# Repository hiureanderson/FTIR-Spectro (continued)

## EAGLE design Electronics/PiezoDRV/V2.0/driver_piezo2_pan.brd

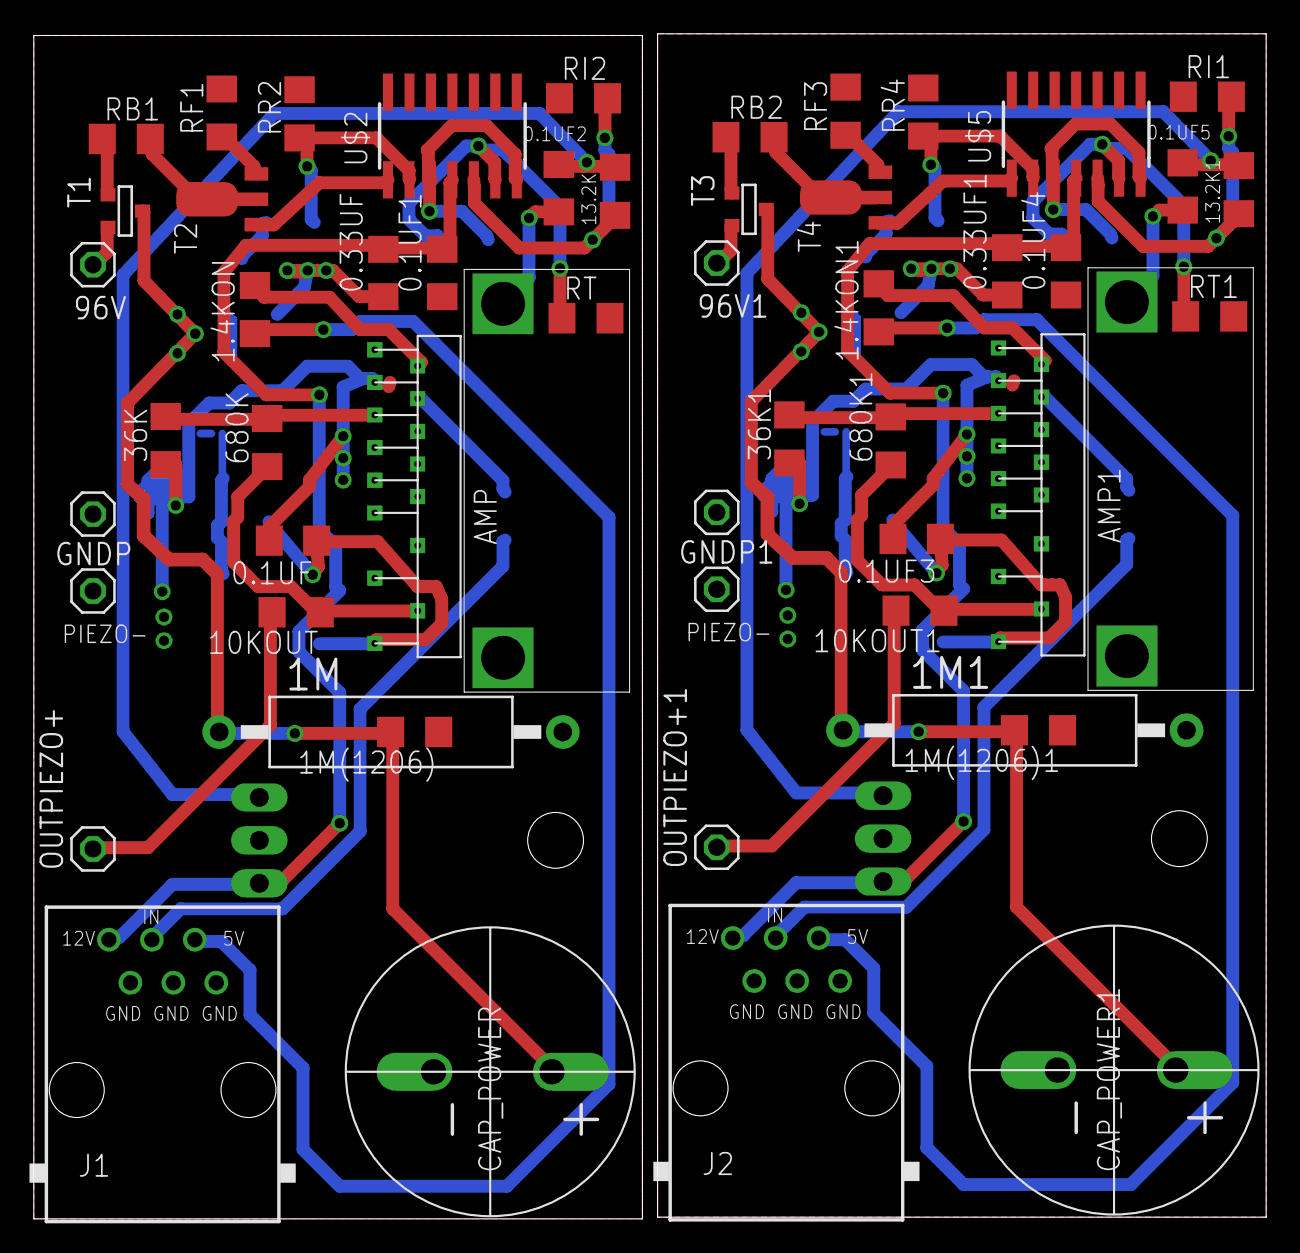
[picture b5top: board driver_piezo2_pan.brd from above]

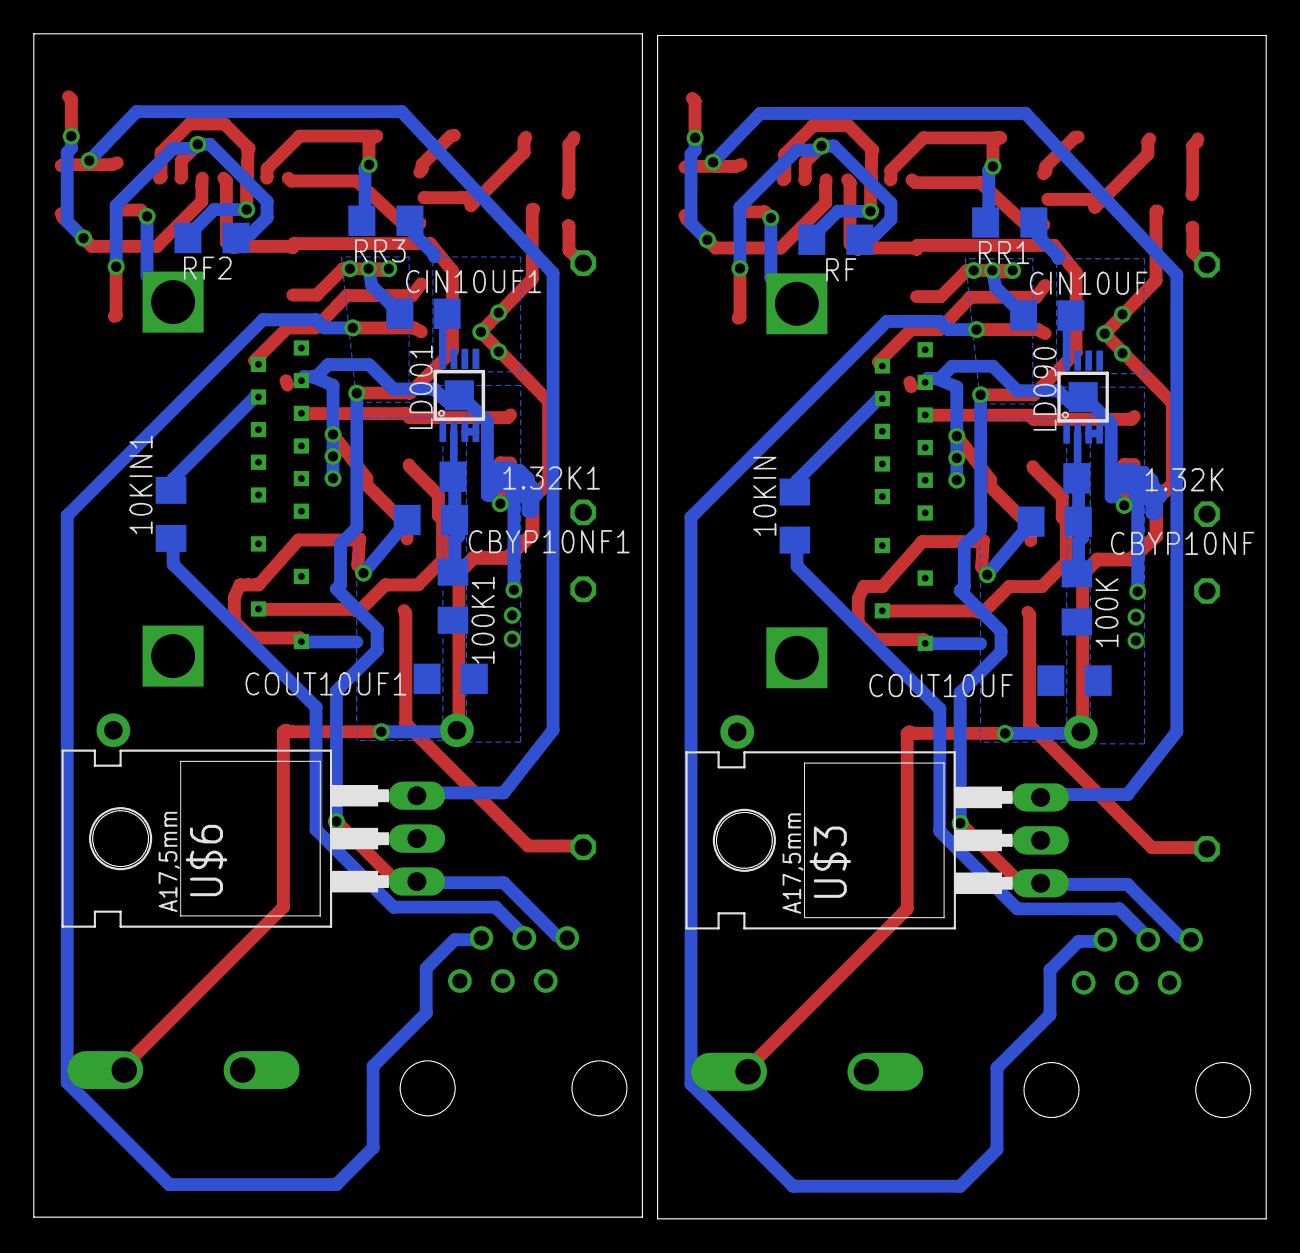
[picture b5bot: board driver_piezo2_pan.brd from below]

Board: 2 copper layers, 72.9 x 70.1 mm, 74 parts (20 on the bottom side), 44 nets.

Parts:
0.1UF, 0.1UF1, 0.1UF2, 0.1UF3, 0.1UF4, 0.1UF5, 0.33UF, 0.33UF1: C1206
1.4KON, 1.4KON1, 1.32K, 1.32K1, 1M(1206), 1M(1206)1, 10KIN, 10KIN1, 10KOUT, 10KOUT1, 36K, 36K1, 100K, 100K1, 680K, 680K1: R1206
1M, 1M1: CA0002
13.2K, 13.2K1: 13.2K; R1206
96V, 96V1: 1X01
AMP, AMP1: POWER_AMP_LME49811TB
CAP_POWER, CAP_POWER1: CAP200VCAP200V; CAP200V
CBYP10NF, CBYP10NF1: C1206
CIN10UF, CIN10UF1: C1206
COUT10UF, COUT10UF1: C1206
GND1, GND2: 1X01
GNDP, GNDP1: 1X01
J1, J2: RJ12STRAIGHT-ANALOG; RJ12-STRAIGHT-ANALOG
LD001, LD090: TPS7A4001; S-PDSO-G08
OUTPIEZO+, OUTPIEZO+1: 1X01
RB1, RB2: 100k; R1206
RF, RF1, RF2, RF3: 10k; R1206
RI1, RI2: 280k; R1206
RR1, RR3: 810k-806k; R1206
RR2, RR4: 90k; R1206
RT, RT1: 10k; R1206
T1, T3: FMMT718; SOT-23
T2, T4: SOT89
U$1, U$4: DISIPADOR
U$2, U$5: LM324; SO14
U$3, U$6: 7805; TO220

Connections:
1OUT: T2.1, U$2.1
1OUT1: T4.1, U$5.1
2IN+: 13.2K.1, RI2.2, U$2.5
2IN+1: 13.2K1.1, RI1.2, U$5.5
2IN-: RF.1, RT.1, U$2.6
2IN-1: RF2.1, RT1.1, U$5.6
2OUT: RF.2, U$2.3, U$2.7
2OUT1: RF2.2, U$5.3, U$5.7
5V: 1.4KON.1, J1.+5V
5V1: 1.4KON1.1, J2.+5V
5VOP: 0.1UF2.2, 13.2K.2, U$3.3
5VOP1: 0.1UF5.2, 13.2K1.2, U$6.3
12V: 0.1UF1.2, 0.33UF.2, J1.+12V, U$2.4, U$3.1
12V1: 0.1UF4.2, 0.33UF1.2, J2.+12V, U$5.4, U$6.1
B: 36K.2, 680K.2, AMP.IN-
B1: 36K1.2, 680K1.2, AMP1.IN-
FB: 1.32K.2, 100K.1, CBYP10NF.2, LD090.2
FB1: 1.32K1.2, 100K1.1, CBYP10NF1.2, LD001.2
GND: 0.1UF.2, 0.1UF1.1, 0.1UF2.1, 0.33UF.1, 1.32K.1, 1M.2, 1M(1206).1, 36K.1, AMP.-VEE, AMP.GND, CAP_POWER.-, CIN10UF.1, COUT10UF.2, GND2.1, GNDP.1, J1.GND1, J1.GND2, J1.GND3, LD090.3, LD090.4, LD090.TH, RF1.2, RI2.1, RR2.2, RT.2, U$1.P$1, U$1.P$2, U$2.11, U$3.2
GND1: 0.1UF3.2, 0.1UF4.1, 0.1UF5.1, 0.33UF1.1, 1.32K1.1, 1M1.2, 1M(1206)1.1, 36K1.1, AMP1.-VEE, AMP1.GND, CAP_POWER1.-, CIN10UF1.1, COUT10UF1.2, GND1.1, GNDP1.1, J2.GND1, J2.GND2, J2.GND3, LD001.3, LD001.4, LD001.TH, RF3.2, RI1.1, RR4.2, RT1.2, U$4.P$1, U$4.P$2, U$5.11, U$6.2
IN_AMP: 10KIN.2, AMP.IN+
IN_AMP1: 10KIN1.2, AMP1.IN+
IN_VOLTAGE: 10KIN.1, J1.IN
IN_VOLTAGE1: 10KIN1.1, J2.IN
unnamed: RB2.2, T4.2, T4.2@1
unnamed: RB2.1, T3.3
unnamed: RB1.2, T2.2, T2.2@1
unnamed: RB1.1, T1.3
unnamed: RF1.1, T2.3
unnamed: RF3.1, T4.3
ON: 1.4KON.2, AMP.SD
ON1: 1.4KON1.2, AMP1.SD
OUT_PIEZO: 10KOUT.2, OUTPIEZO+.1
OUT_PIEZO1: 10KOUT1.2, OUTPIEZO+1.1
SOURCE: 10KOUT.1, 680K.1, AMP.SOURCE
SOURCE1: 10KOUT1.1, 680K1.1, AMP1.SOURCE
V1: 0.1UF3.1, 100K1.2, AMP1.VCC, CBYP10NF1.1, COUT10UF1.1, LD001.1
V90: 0.1UF.1, 100K.2, AMP.VCC, CBYP10NF.1, COUT10UF.1, LD090.1
VF: RR1.2, RR2.1, U$2.2
VF1: RR3.2, RR4.1, U$5.2
VIN: 1M.1, 1M(1206).2, CAP_POWER.+, CIN10UF.2, LD090.5, LD090.8, RR1.1, T1.1
VIN1: 1M1.1, 1M(1206)1.2, CAP_POWER1.+, CIN10UF1.2, LD001.5, LD001.8, RR3.1, T3.1
VINS: 96V.1, T1.2
VINS1: 96V1.1, T3.2

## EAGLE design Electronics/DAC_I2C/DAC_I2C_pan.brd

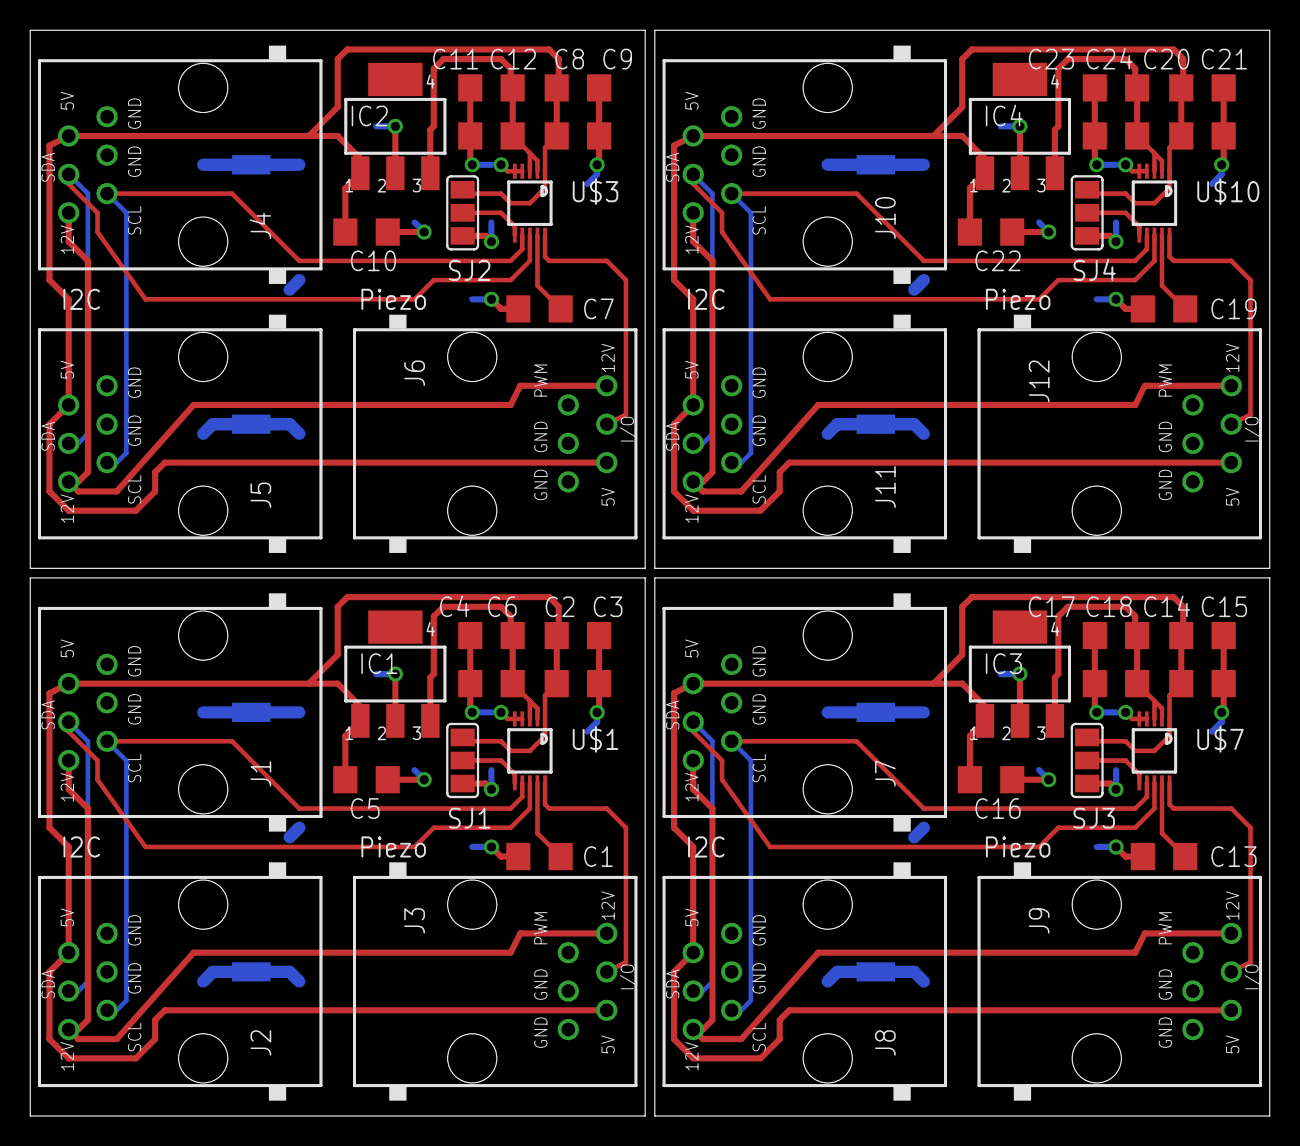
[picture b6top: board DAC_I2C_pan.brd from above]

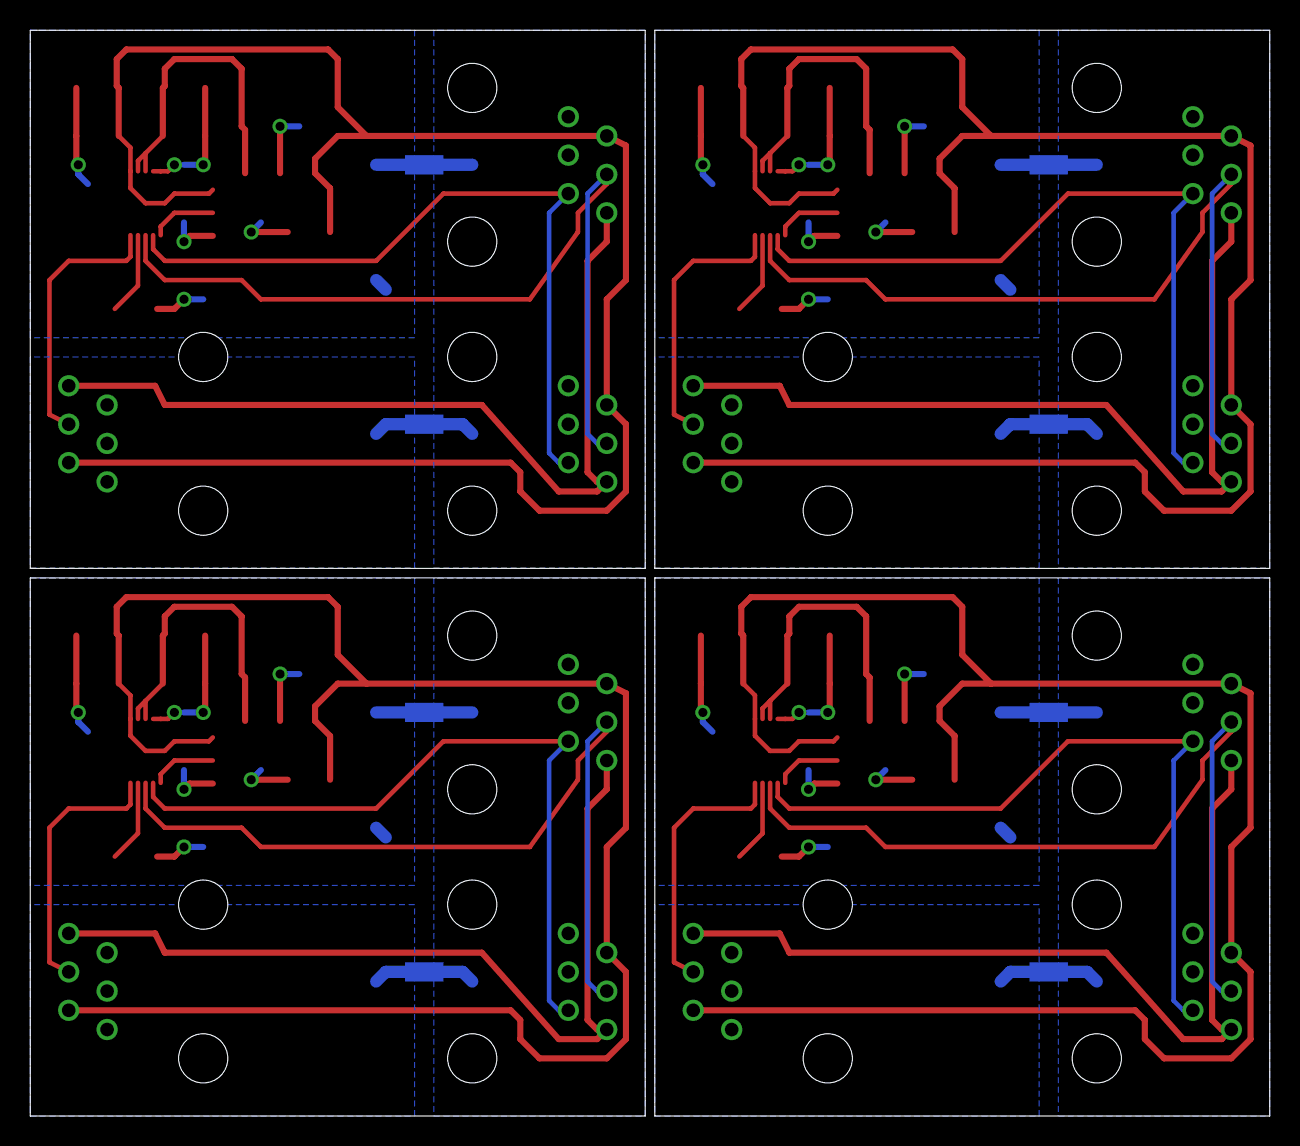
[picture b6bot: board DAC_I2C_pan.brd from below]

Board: 2 copper layers, 81.9 x 71.8 mm, 56 parts (8 on the bottom side), 44 nets.

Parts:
C1, C7, C13, C19: 10n; C1206
C2, C6, C8, C12, C14, C18, C20, C24: 100n; C1206
C3, C9, C15, C21: 10u; C1206
C4, C5, C10, C11, C16, C17, C22, C23: 10uF; C1206
IC1, IC2, IC3, IC4: MCP1703DB; SOT223
J1, J2, J4, J5, J7, J8, J10, J11: RJ12STRAIGHT-I2C; RJ12-STRAIGHT-I2C
J3, J6, J9, J12: RJ12STRAIGHT; RJ12-STRAIGHT
SJ1, SJ2, SJ3, SJ4: SJ_2
U$1, U$3, U$7, U$10: AD5693R; MSOP10
U$2, U$4, U$5, U$6, U$8, U$9, U$11, U$12: STARGND; STAR

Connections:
3.3V: C4.1, C6.1, IC1.3, U$1.2, U$1.3
3.3V1: C11.1, C12.1, IC2.3, U$3.2, U$3.3
3.3V2: C17.1, C18.1, IC3.3, U$7.2, U$7.3
3.3V3: C23.1, C24.1, IC4.3, U$10.2, U$10.3
AGND: C1.2, C2.2, C3.2, C4.2, C5.2, C6.2, IC1.2, SJ1.3, U$1.4, U$1.5, U$5.AGND
AGND1: C7.2, C8.2, C9.2, C10.2, C11.2, C12.2, IC2.2, SJ2.3, U$3.4, U$3.5, U$4.AGND
AGND2: C13.2, C14.2, C15.2, C16.2, C17.2, C18.2, IC3.2, SJ3.3, U$7.4, U$7.5, U$8.AGND
AGND3: C19.2, C20.2, C21.2, C22.2, C23.2, C24.2, IC4.2, SJ4.3, U$10.4, U$10.5, U$11.AGND
DGND: J1.GND1, J1.GND2, J2.GND1, J2.GND2, U$2.DGND, U$2.GND, U$5.DGND, U$5.GND
DGND1: J4.GND1, J4.GND2, J5.GND1, J5.GND2, U$4.DGND, U$4.GND, U$6.DGND, U$6.GND
DGND2: J7.GND1, J7.GND2, J8.GND1, J8.GND2, U$8.DGND, U$8.GND, U$9.DGND, U$9.GND
DGND3: J10.GND1, J10.GND2, J11.GND1, J11.GND2, U$11.DGND, U$11.GND, U$12.DGND, U$12.GND
GND: J3.GND1, J3.GND2, U$2.AGND
GND1: J6.GND1, J6.GND2, U$6.AGND
GND2: J9.GND1, J9.GND2, U$9.AGND
GND3: J12.GND1, J12.GND2, U$12.AGND
unnamed: SJ1.2, U$1.6
unnamed: SJ2.2, U$3.6
unnamed: SJ3.2, U$7.6
unnamed: SJ4.2, U$10.6
SCL: J1.SCL, J2.SCL, U$1.7
SCL1: J4.SCL, J5.SCL, U$3.7
SCL2: J7.SCL, J8.SCL, U$7.7
SCL3: J10.SCL, J11.SCL, U$10.7
SDA: J1.SDA, J2.SDA, U$1.8
SDA1: J4.SDA, J5.SDA, U$3.8
SDA2: J7.SDA, J8.SDA, U$7.8
SDA3: J10.SDA, J11.SDA, U$10.8
VCC: C2.1, C3.1, C5.1, IC1.1, J1.+5V, J2.+5V, J3.+5V, SJ1.1, U$1.1
VCC1: C8.1, C9.1, C10.1, IC2.1, J4.+5V, J5.+5V, J6.+5V, SJ2.1, U$3.1
VCC2: C14.1, C15.1, C16.1, IC3.1, J7.+5V, J8.+5V, J9.+5V, SJ3.1, U$7.1
VCC3: C20.1, C21.1, C22.1, IC4.1, J10.+5V, J11.+5V, J12.+5V, SJ4.1, U$10.1
VDD: J1.+12V, J2.+12V, J3.+12V
VDD1: J4.+12V, J5.+12V, J6.+12V
VDD2: J7.+12V, J8.+12V, J9.+12V
VDD3: J10.+12V, J11.+12V, J12.+12V
VOUT: J3.I/O, U$1.10
VOUT1: J6.I/O, U$3.10
VOUT2: J9.I/O, U$7.10
VOUT3: J12.I/O, U$10.10
VREF: C1.1, U$1.9
VREF1: C7.1, U$3.9
VREF2: C13.1, U$7.9
VREF3: C19.1, U$10.9

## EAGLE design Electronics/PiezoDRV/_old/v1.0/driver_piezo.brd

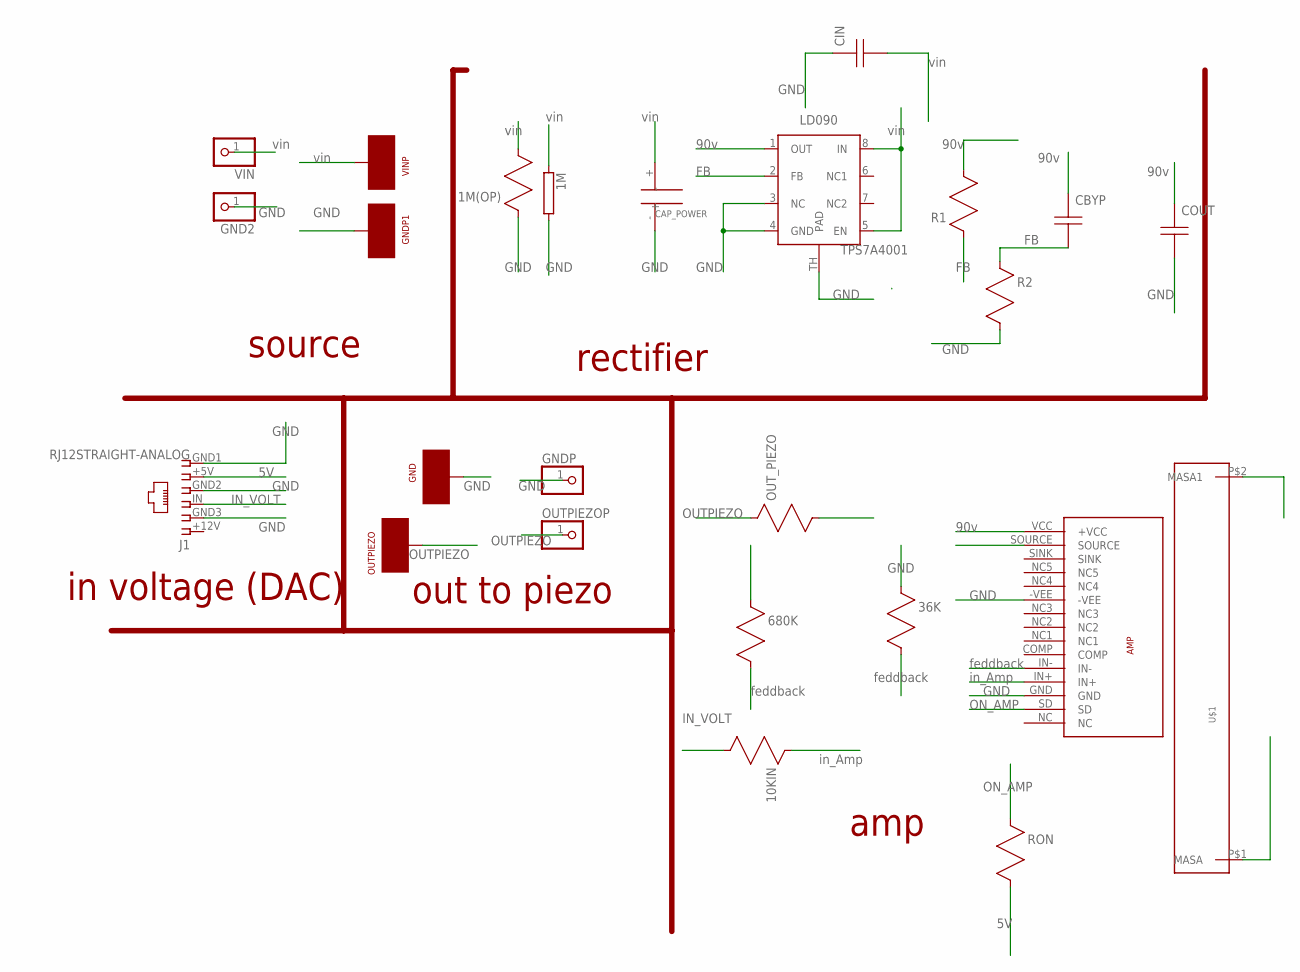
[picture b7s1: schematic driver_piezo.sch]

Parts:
1M: RCA0002; CA0002
1M(OP), 10KIN, 36K, 680K: RES; R0805
AMP: POWER_AMP_LME49811TB
CAP_POWER: CAP200VCAP200V; CAP200V
CBYP: CAP; C0805
CIN: CAP; C0805
COUT: CAP; C0805
GND: PAD
GND2: PINHD-1X1; 1X01
GNDP: PINHD-1X1; 1X01
GNDP1: PAD
J1: RJ12STRAIGHT-ANALOG; RJ12-STRAIGHT-ANALOG
LD090: TPS7A4001; S-PDSO-G08
OUTPIEZO: PAD
OUTPIEZOP: PINHD-1X1; 1X01
OUT_PIEZO: RES; R0805
R1, R2: RES; R0805
RON: RES; R0805
U$1: DISIPADOR
VIN: PINHD-1X1; 1X01
VINP: PAD

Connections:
5V: J1.+5V (5), RON.2 (B)
B: 36K.2 (B), 680K.2 (B), AMP.IN-
FB: CBYP.2 (B), LD090.2 (FB), R1.1 (A), R2.1 (A)
GND: 1M.2, 1M(OP).1 (A), 36K.1 (A), AMP.-VEE, AMP.GND, CAP_POWER.-, CIN.1 (A), COUT.2 (B), GND.P$1, GND2.1, GNDP.1, GNDP1.P$1, J1.GND1 (6), J1.GND2 (4), J1.GND3 (2), LD090.3 (NC), LD090.4 (GND), LD090.TH (PAD), R2.2 (B), U$1.P$1 (MASA), U$1.P$2 (MASA1)
IN_AMP: 10KIN.1 (A), AMP.IN+
IN_VOLTAGE: 10KIN.2 (B), J1.IN (3)
ON: AMP.SD, RON.1 (A)
OUT_PIEZO: OUTPIEZO.P$1, OUTPIEZOP.1, OUT_PIEZO.1 (A)
SOURCE: 680K.1 (A), AMP.SOURCE, OUT_PIEZO.2 (B)
V90: AMP.VCC (+VCC), CBYP.1 (A), COUT.1 (A), LD090.1 (OUT), R1.2 (B)
VIN: 1M.1, 1M(OP).2 (B), CAP_POWER.+, CIN.2 (B), LD090.5 (EN), LD090.8 (IN), VIN.1, VINP.P$1

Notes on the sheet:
source
rectifier
out to piezo
amp
vin
90v
GND
OUTPIEZO
IN_VOLT
ON_AMP
feddback
in voltage (DAC)
in_Amp

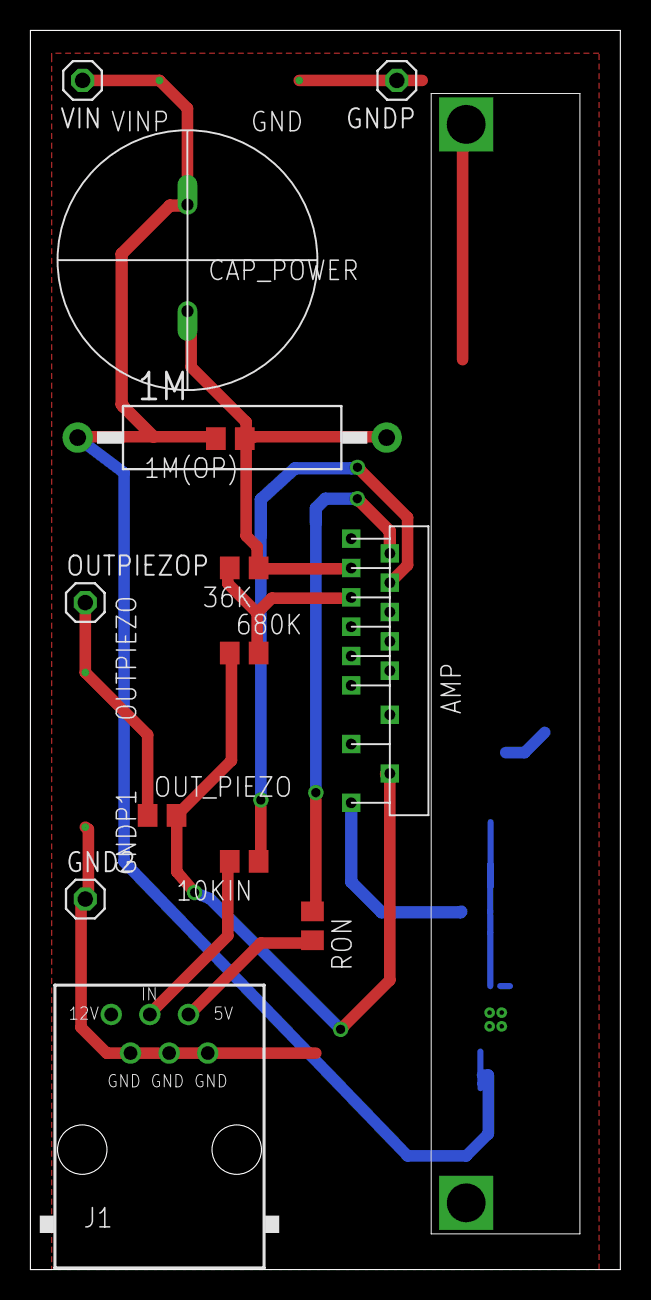
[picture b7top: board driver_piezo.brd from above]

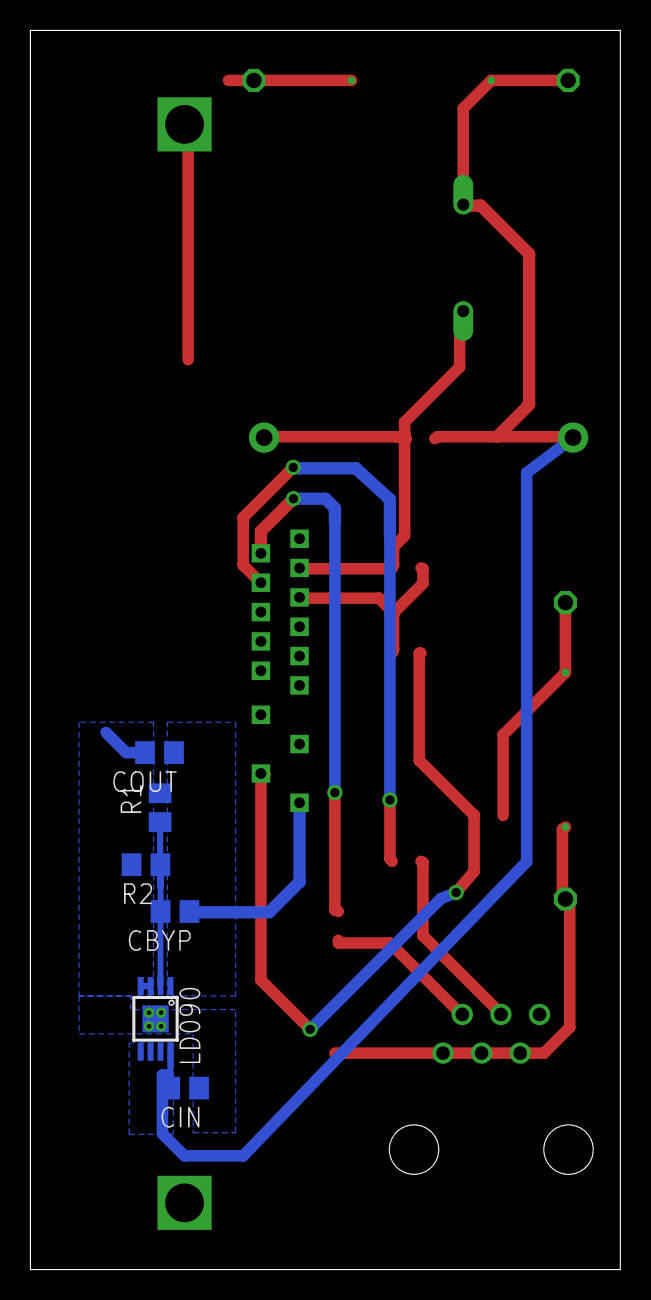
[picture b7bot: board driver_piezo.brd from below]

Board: 2 copper layers, 38.8 x 81.5 mm, 25 parts (6 on the bottom side), 11 nets.

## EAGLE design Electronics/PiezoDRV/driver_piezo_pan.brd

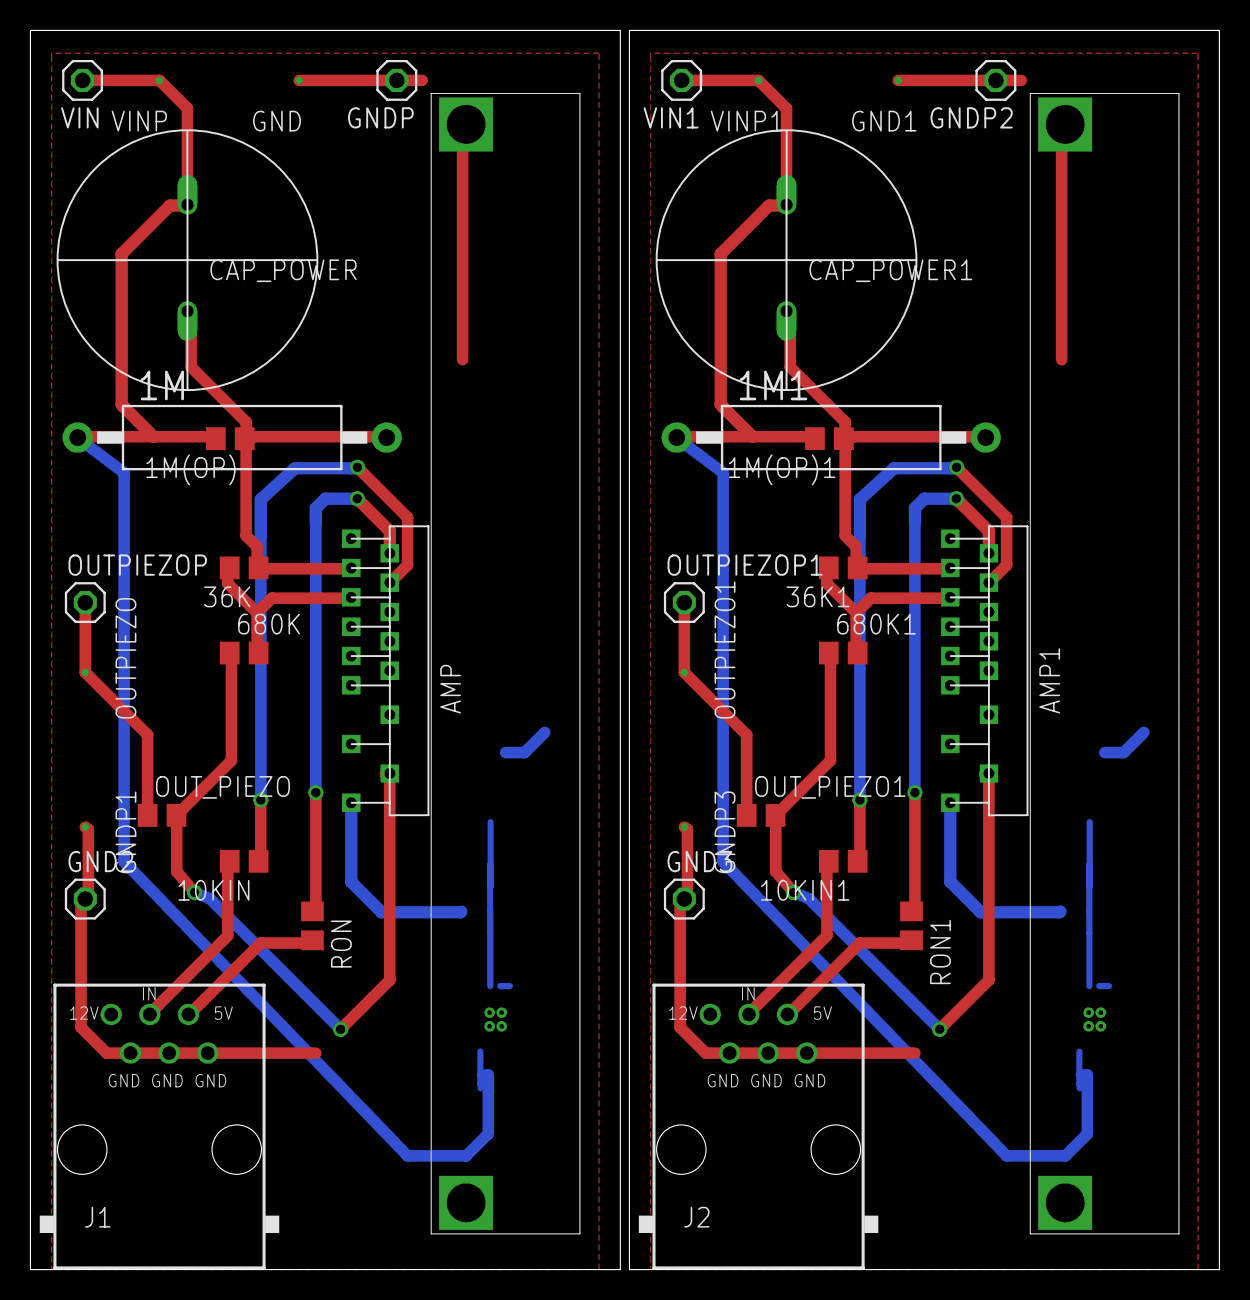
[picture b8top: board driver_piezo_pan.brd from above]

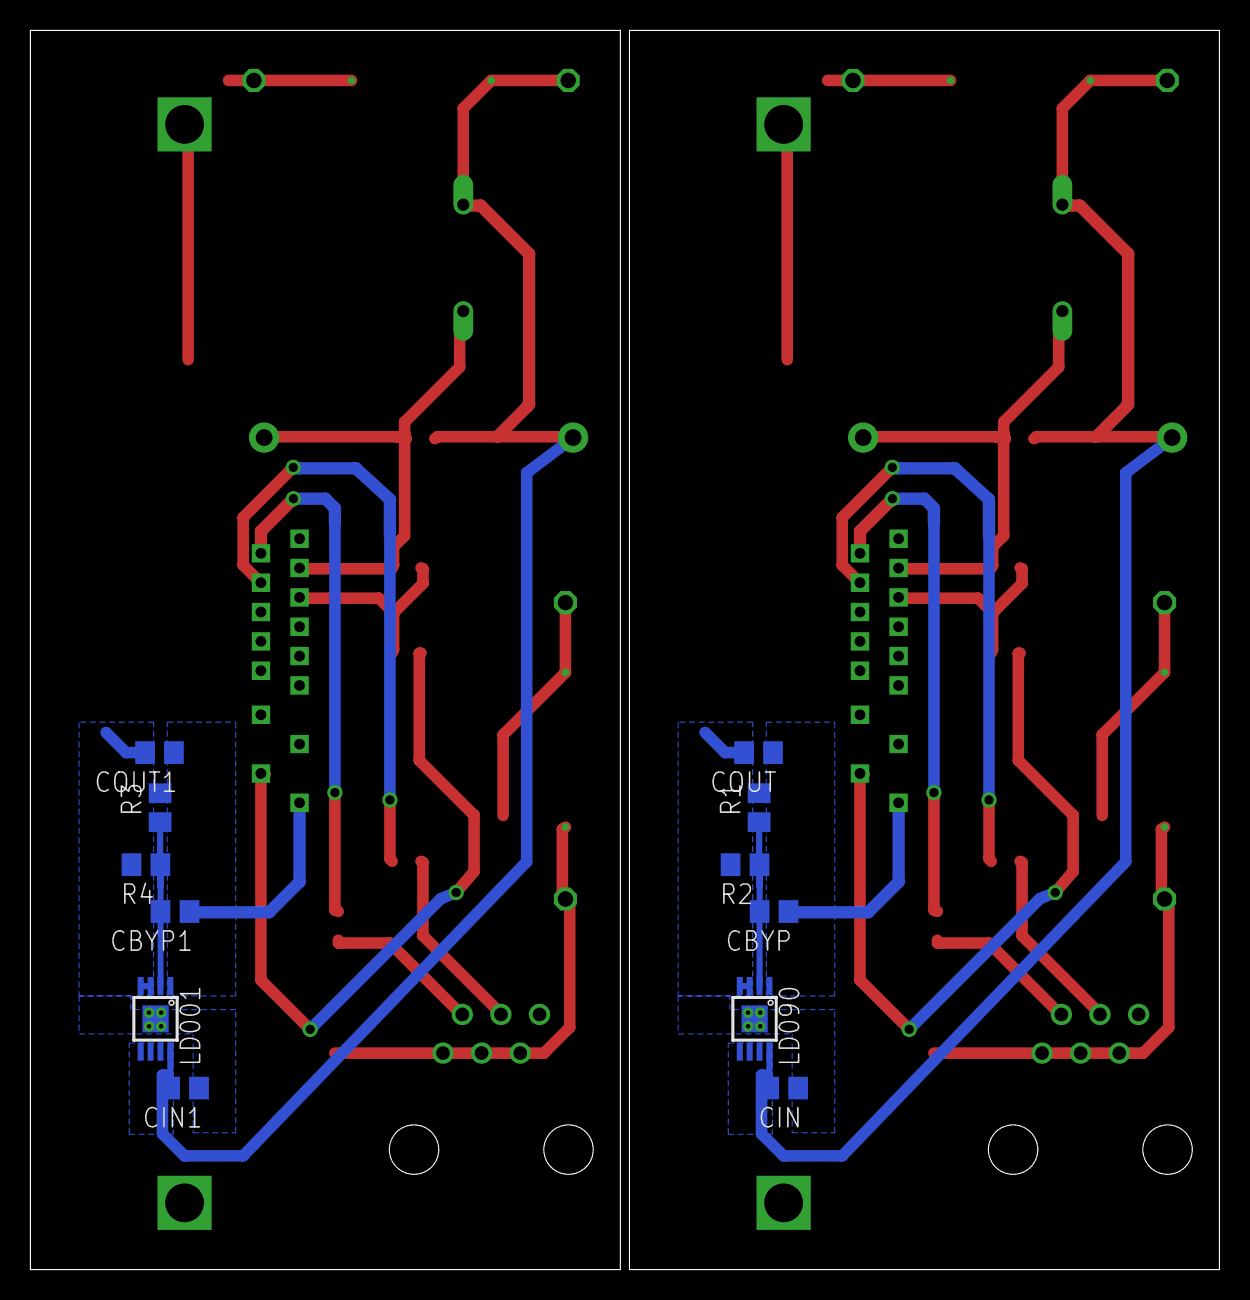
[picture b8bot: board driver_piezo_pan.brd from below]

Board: 2 copper layers, 78.2 x 81.5 mm, 50 parts (12 on the bottom side), 22 nets.

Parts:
1M, 1M1: CA0002
1M(OP), 1M(OP)1, 10KIN, 10KIN1, 36K, 36K1, 680K, 680K1: R0805
AMP, AMP1: POWER_AMP_LME49811TB
CAP_POWER, CAP_POWER1: CAP200VCAP200V; CAP200V
CBYP, CBYP1: C0805
CIN, CIN1: C0805
COUT, COUT1: C0805
GND, GND1: PAD
GND2, GND3: 1X01
GNDP, GNDP2: 1X01
GNDP1, GNDP3: PAD
J1, J2: RJ12STRAIGHT-ANALOG; RJ12-STRAIGHT-ANALOG
LD001, LD090: TPS7A4001; S-PDSO-G08
OUTPIEZO, OUTPIEZO1: PAD
OUTPIEZOP, OUTPIEZOP1: 1X01
OUT_PIEZO, OUT_PIEZO1: R0805
R1, R2, R3, R4: R0805
RON, RON1: R0805
U$1, U$2: DISIPADOR
VIN, VIN1: 1X01
VINP, VINP1: PAD

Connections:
5V: J1.+5V, RON.2
5V1: J2.+5V, RON1.2
B: 36K.2, 680K.2, AMP.IN-
B1: 36K1.2, 680K1.2, AMP1.IN-
FB: CBYP.2, LD090.2, R1.1, R2.1
FB1: CBYP1.2, LD001.2, R3.1, R4.1
GND: 1M.2, 1M(OP).1, 36K.1, AMP.-VEE, AMP.GND, CAP_POWER.-, CIN.1, COUT.2, GND.P$1, GND2.1, GNDP.1, GNDP1.P$1, J1.GND1, J1.GND2, J1.GND3, LD090.3, LD090.4, LD090.TH, R2.2, U$1.P$1, U$1.P$2
GND1: 1M1.2, 1M(OP)1.1, 36K1.1, AMP1.-VEE, AMP1.GND, CAP_POWER1.-, CIN1.1, COUT1.2, GND1.P$1, GND3.1, GNDP2.1, GNDP3.P$1, J2.GND1, J2.GND2, J2.GND3, LD001.3, LD001.4, LD001.TH, R4.2, U$2.P$1, U$2.P$2
IN_AMP: 10KIN.1, AMP.IN+
IN_AMP1: 10KIN1.1, AMP1.IN+
IN_VOLTAGE: 10KIN.2, J1.IN
IN_VOLTAGE1: 10KIN1.2, J2.IN
ON: AMP.SD, RON.1
ON1: AMP1.SD, RON1.1
OUT_PIEZO: OUTPIEZO.P$1, OUTPIEZOP.1, OUT_PIEZO.1
OUT_PIEZO1: OUTPIEZO1.P$1, OUTPIEZOP1.1, OUT_PIEZO1.1
SOURCE: 680K.1, AMP.SOURCE, OUT_PIEZO.2
SOURCE1: 680K1.1, AMP1.SOURCE, OUT_PIEZO1.2
V1: AMP1.VCC, CBYP1.1, COUT1.1, LD001.1, R3.2
V90: AMP.VCC, CBYP.1, COUT.1, LD090.1, R1.2
VIN: 1M.1, 1M(OP).2, CAP_POWER.+, CIN.2, LD090.5, LD090.8, VIN.1, VINP.P$1
VIN1: 1M1.1, 1M(OP)1.2, CAP_POWER1.+, CIN1.2, LD001.5, LD001.8, VIN1.1, VINP1.P$1

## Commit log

2015-07-16 first push with incomplete CAD files and datasheets
2015-07-17 CAD work on progress, missing splitter hat screws and sensor support
2015-07-18 CAD almost done, minor correction on Splitter_Hat_1 to come
2015-07-19 corrected hat, added assembled and split views
2015-07-21 IR source T°C at 120°C : corrected bench design, added 2D woodcuts as heat insulators to protect ABS prints
2015-07-26 added heat sink to the design
2015-07-28 started main board design
2015-07-28 Create DAC20
    DAC 20 bits device
2015-08-02 started electronic design of the main board
2015-08-04 main board Oudini on the way, 2.5V ref generator missing for the DAC stage, guard ring to be added on C1 C2 (see datasheet DAC1220)
2015-08-05 finalisation of main FTIR board (Oudini)
2015-08-06 finished sensor board for D205B, finished main board Oudini v1.0, Generated Gerbers, modified CAD for PCB support
2015-08-10 added slit for piezo driver PCB, actualized lpatini.lbr
2015-08-11 added piezo driver, slight change on the optical bench CAD
2015-08-12 starting the mainboard Firmware
2015-08-12 finished pin mapping
2015-09-01 started assembly, some code modifications according to SolarBoard (locker, small log) need to reduce the log further and code the scanning routine
2015-09-04 changed pin mapping, PID need to be remanufactured (too low thermal insulation between hot and cold)
2015-09-12 modified logger I2C to avoid crash on memory erase, added test code for the IR sensor P205B
2015-09-12 added buying list from Shenzhen
2015-09-19 initiated code for DAC1220 contorl over SPI, need to review the log (log-on-step) & disable wdt on memory swipe & end DAC1220 configure
2015-09-19 added configuration code and stepping code for DAC1220, yield a 2.5-5V variation over 65535 steps
2015-09-19 added images of the system
2015-09-24 added 96 voltage stabilizer t othe Piezo Driver Board
2015-09-25 development board for MSOP10 16 bits I2C DAC
2015-09-25 corrections on piezo driver v2.0, generated gerbers
2016-08-27 update project current state and TODOs
